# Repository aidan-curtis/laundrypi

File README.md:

Compile spidev_pi.c on raspberry pi with "gcc spidev_pi.c -o spidev_pi".
Run program with "./spidev_pi".

Used: MSP430G2553 (20 pin SMD package), Raspberry Pi 3 Model B+ (2017)

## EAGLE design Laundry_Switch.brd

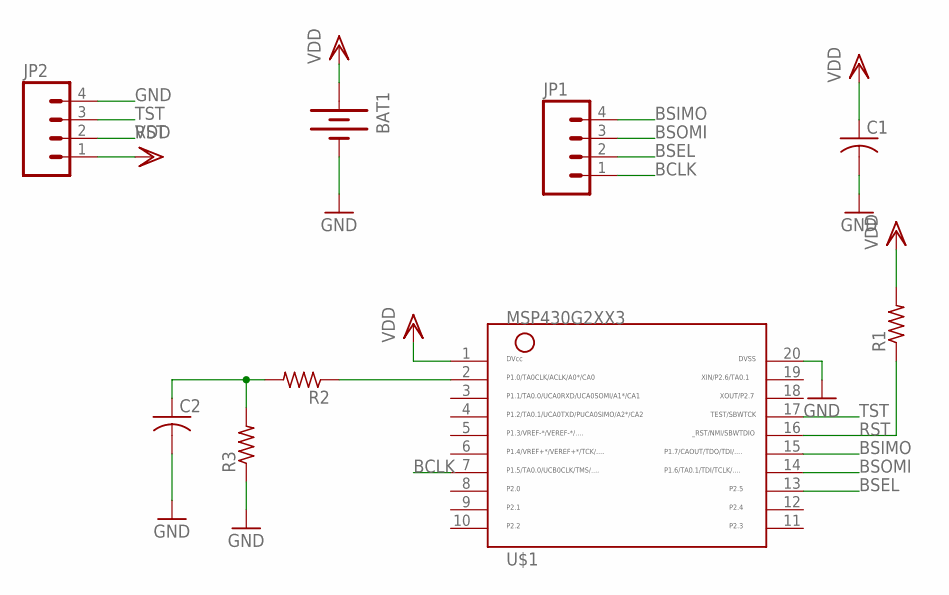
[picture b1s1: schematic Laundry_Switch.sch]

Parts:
BAT1: BATTERYBU2032SM; BU2032SM
C1: RCL_C-USC1206; RCL_C1206
C2: C-US050-050X075; C050-050X075
JP1, JP2: PENDANT_M04LOCK; PENDANT_1X04_LOCK
R1, R2, R3: RCL_R-US_R1206; RCL_R1206
U$1: MSP430G2XX3TSSOP; PW20

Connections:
BCLK: JP1.1, U$1.7
BSEL: JP1.2, U$1.13
BSIMO: JP1.4, U$1.15
BSOMI: JP1.3, U$1.14
GND: BAT1.P$2 (-), C1.2, C2.2, JP2.4, R3.1, U$1.20
unnamed: R2.1, U$1.2
unnamed: C2.1, R2.2, R3.2
RST: JP2.2, R1.1, U$1.16
TST: JP2.3, U$1.17
VDD: BAT1.P$1 (+), C1.1, JP2.1, R1.2, U$1.1

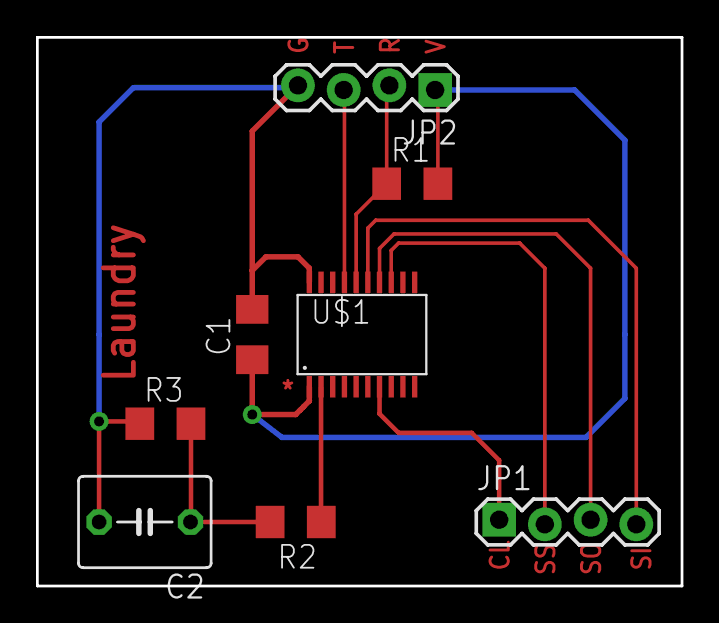
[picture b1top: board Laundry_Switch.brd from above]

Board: 2 copper layers, 35.8 x 30.5 mm, 9 parts (1 on the bottom side), 10 nets.

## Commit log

2018-04-18 first
2018-04-18 message
2018-04-22 asdfd
2018-04-23 woieufne
2018-05-01 Everything working
2018-05-01 Added board,schematic,datasheet for sensor, QR codes
2018-05-01 asdf
2018-05-01 app code and server code
